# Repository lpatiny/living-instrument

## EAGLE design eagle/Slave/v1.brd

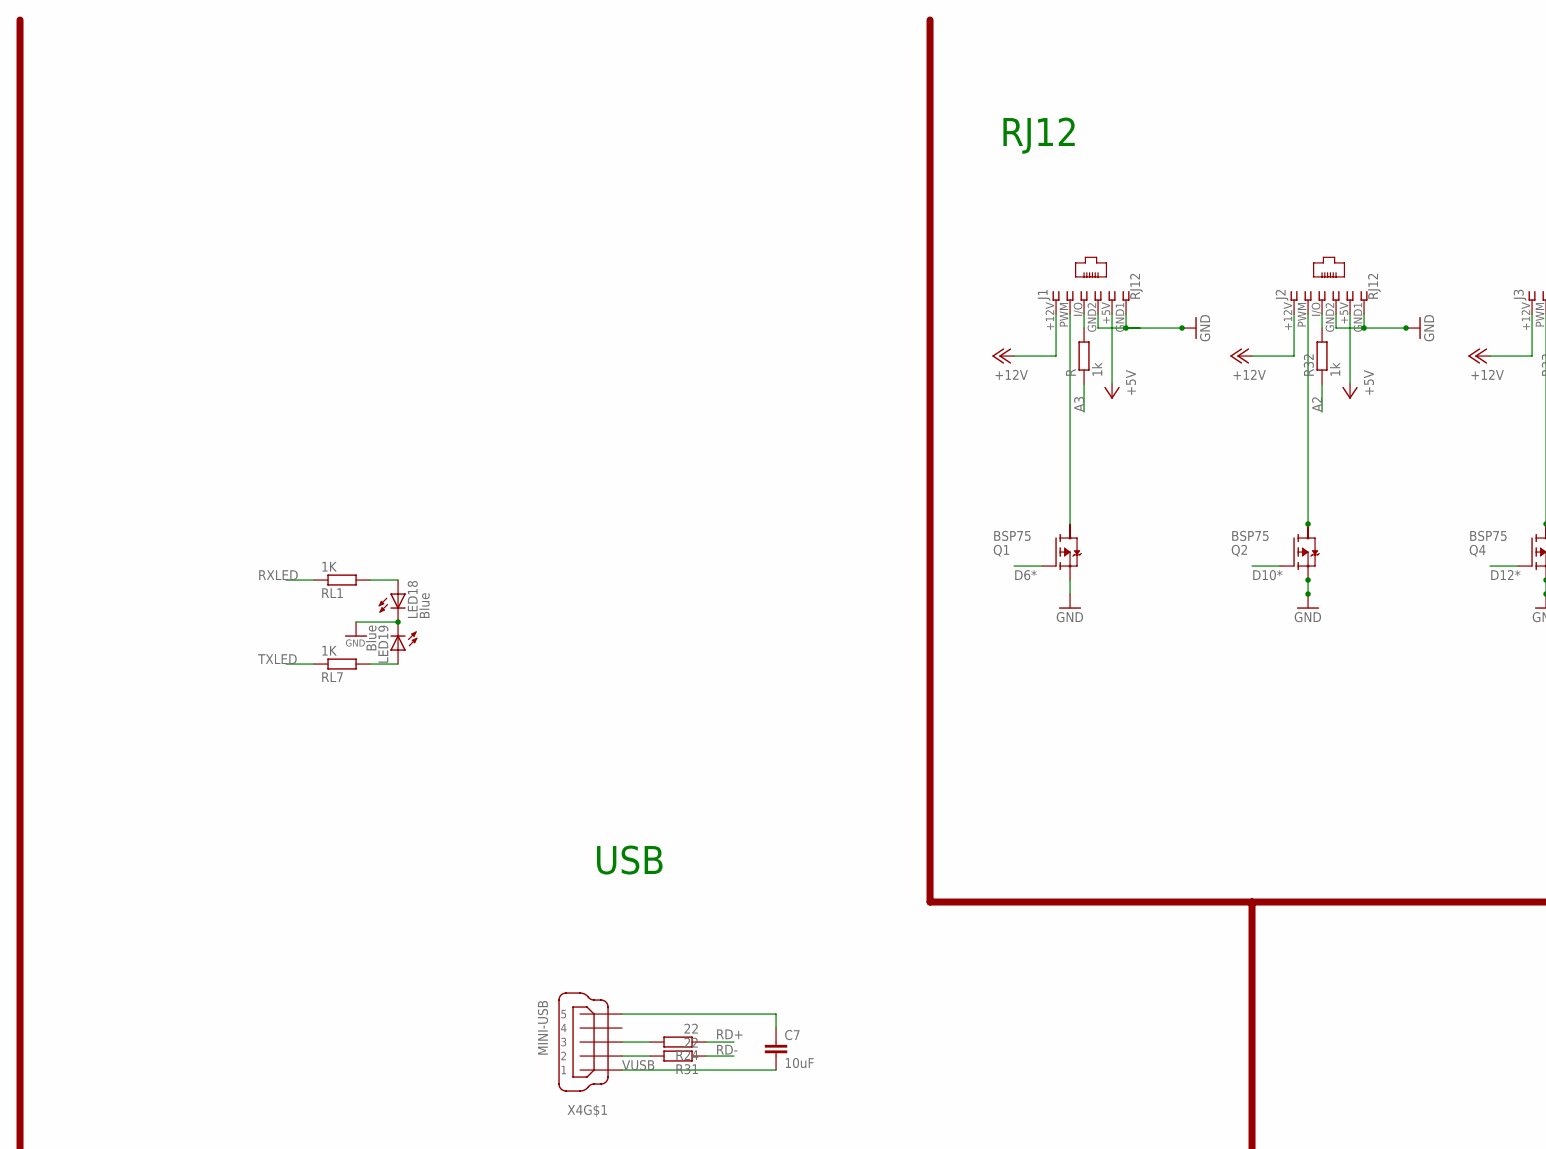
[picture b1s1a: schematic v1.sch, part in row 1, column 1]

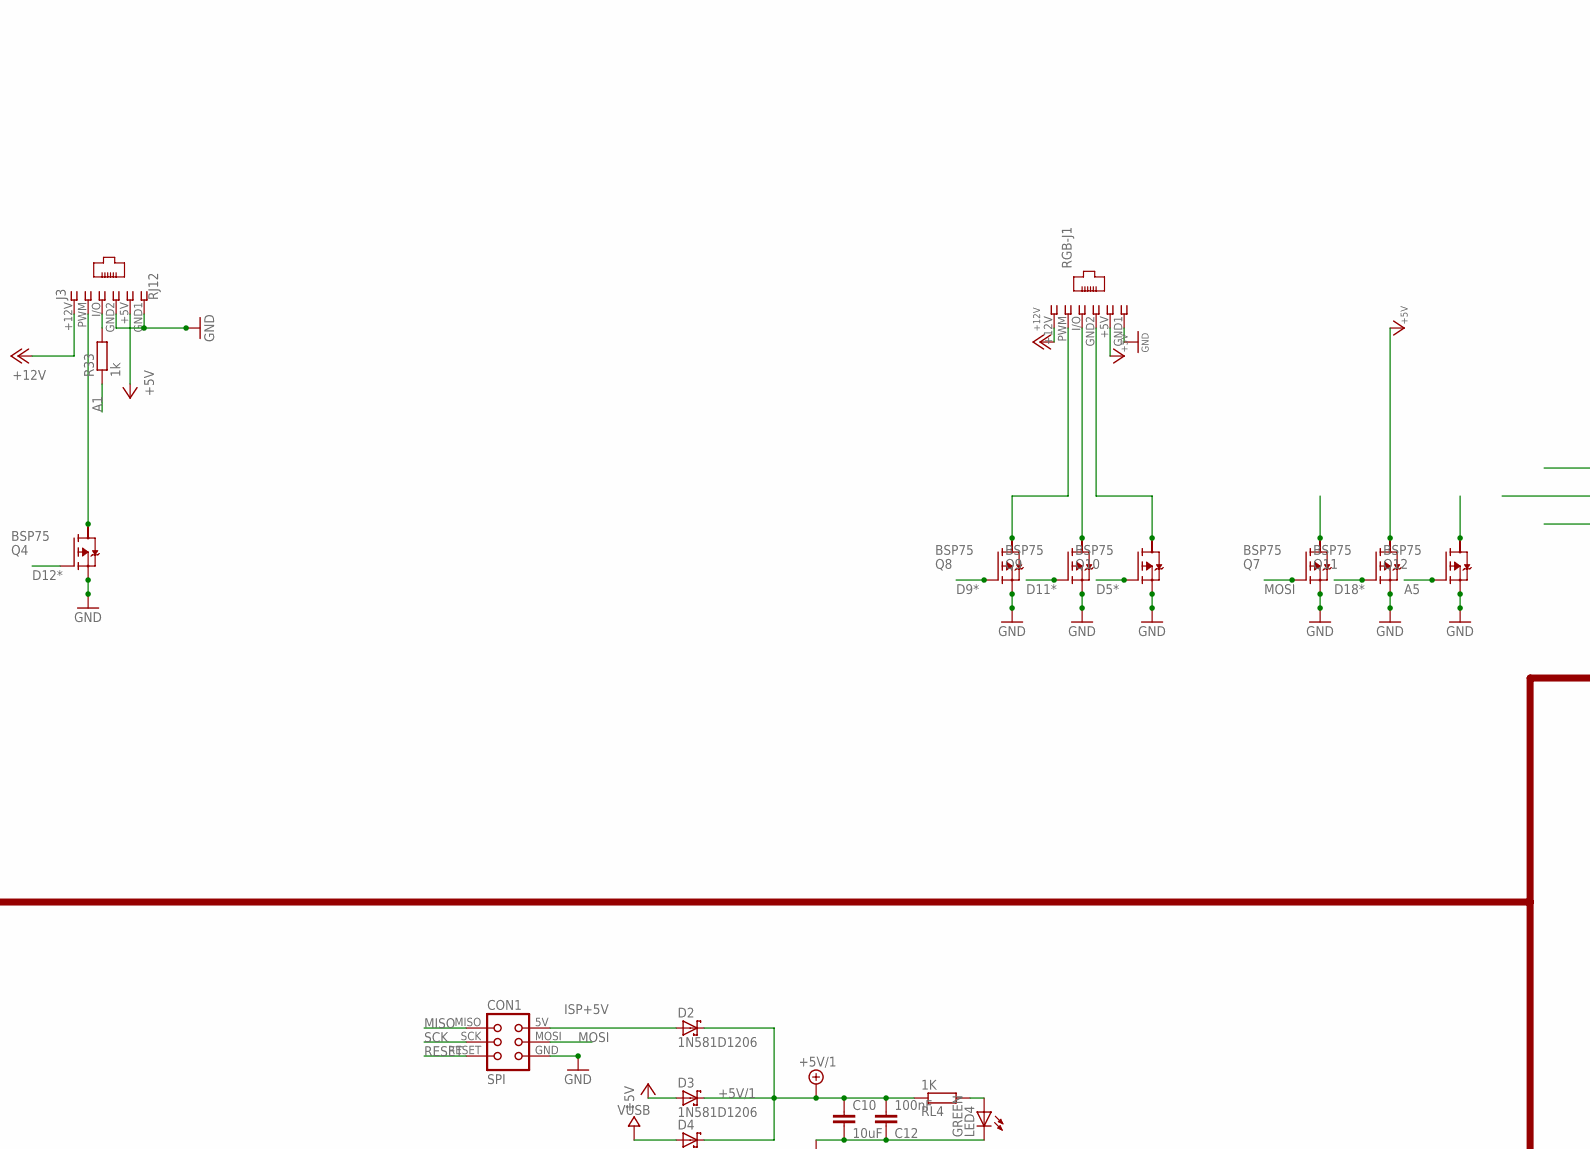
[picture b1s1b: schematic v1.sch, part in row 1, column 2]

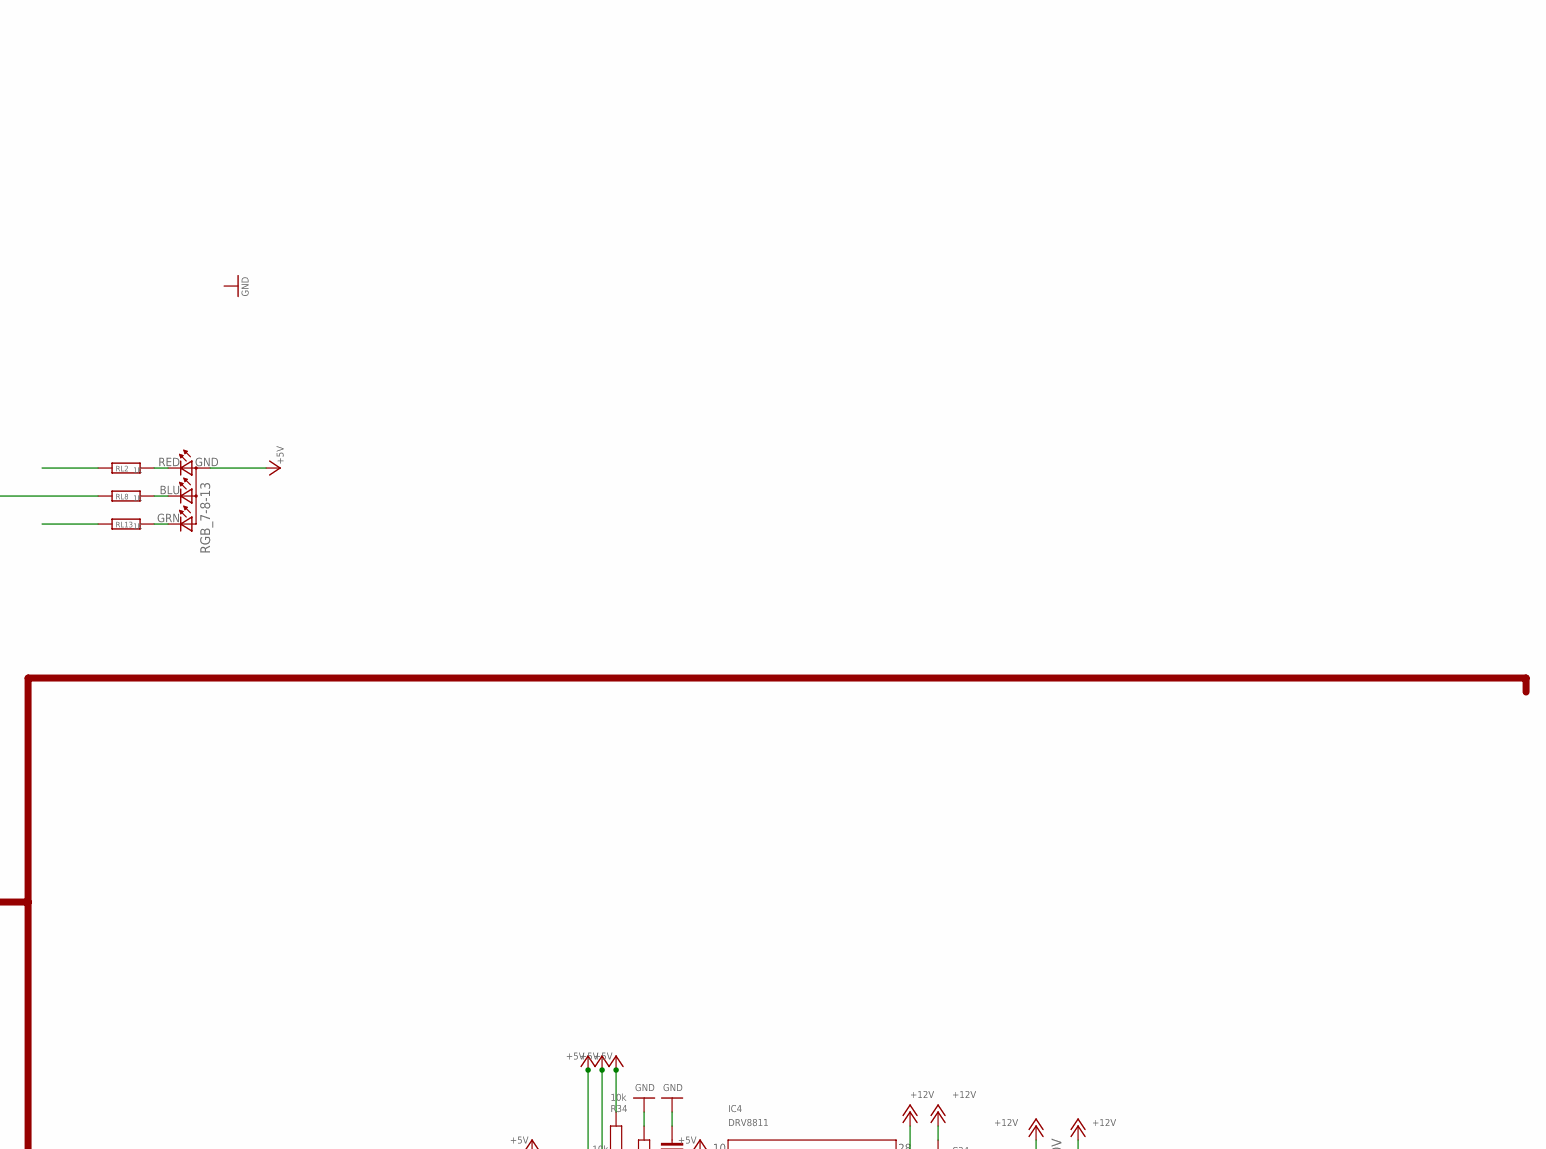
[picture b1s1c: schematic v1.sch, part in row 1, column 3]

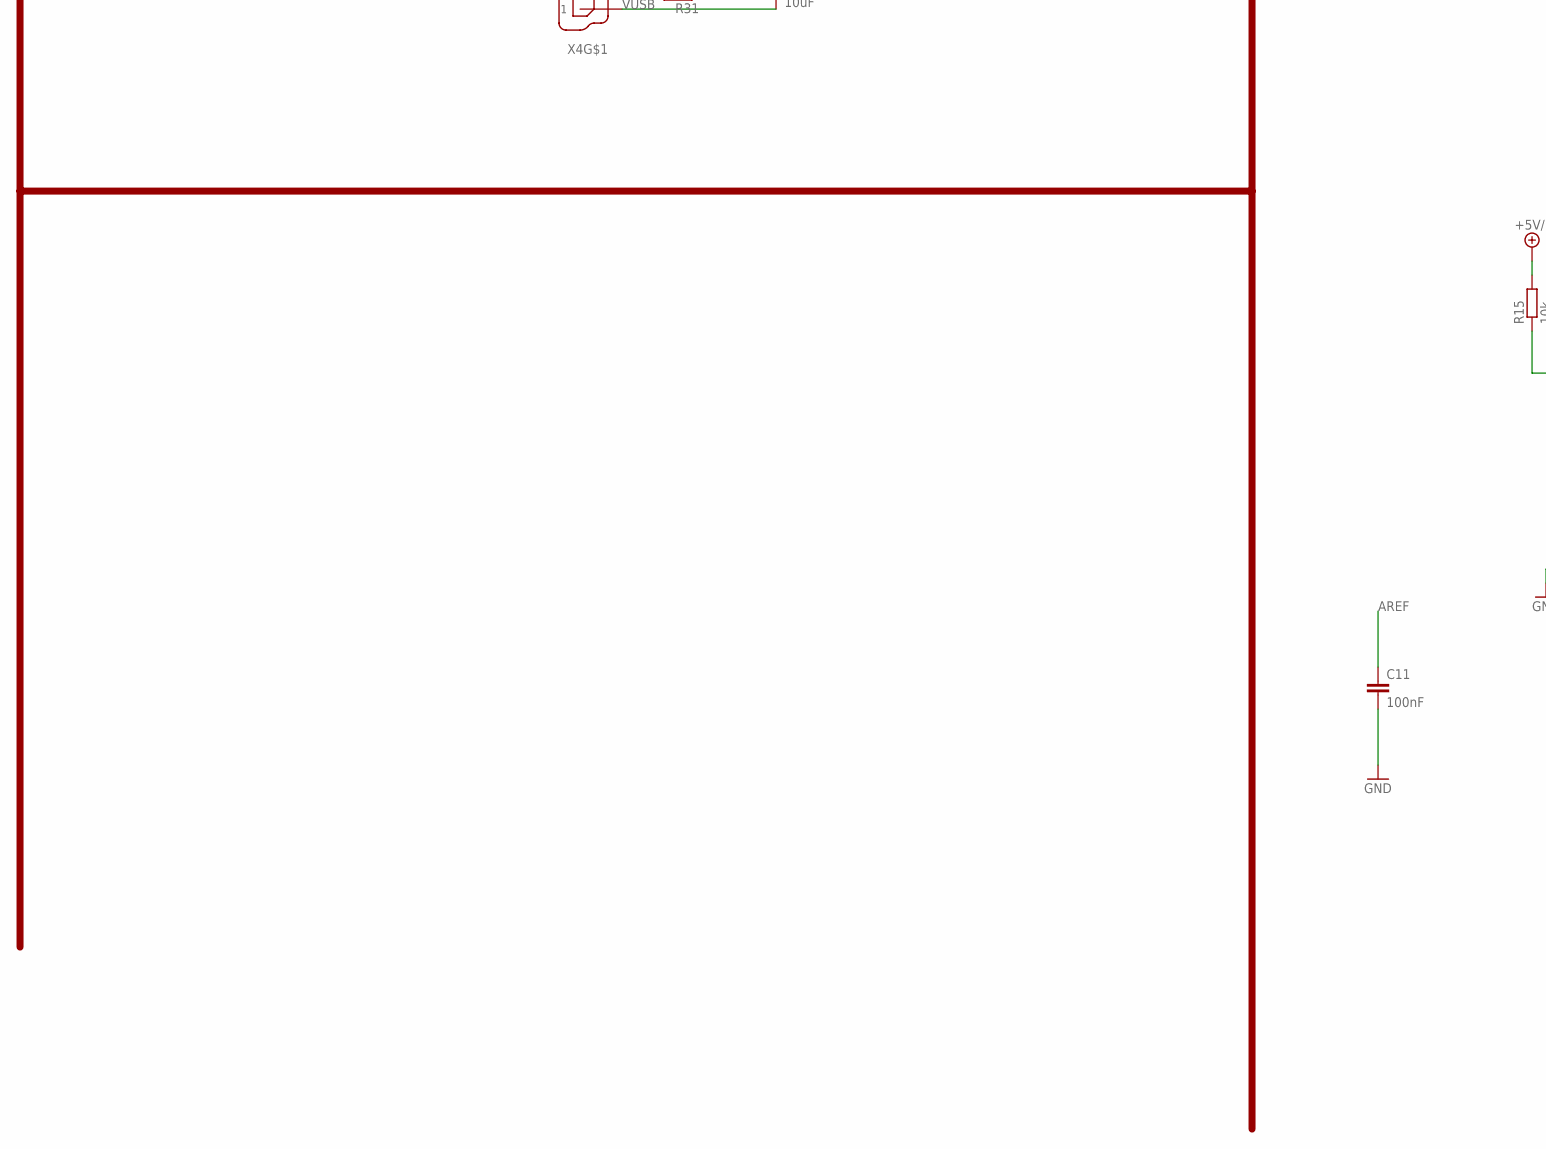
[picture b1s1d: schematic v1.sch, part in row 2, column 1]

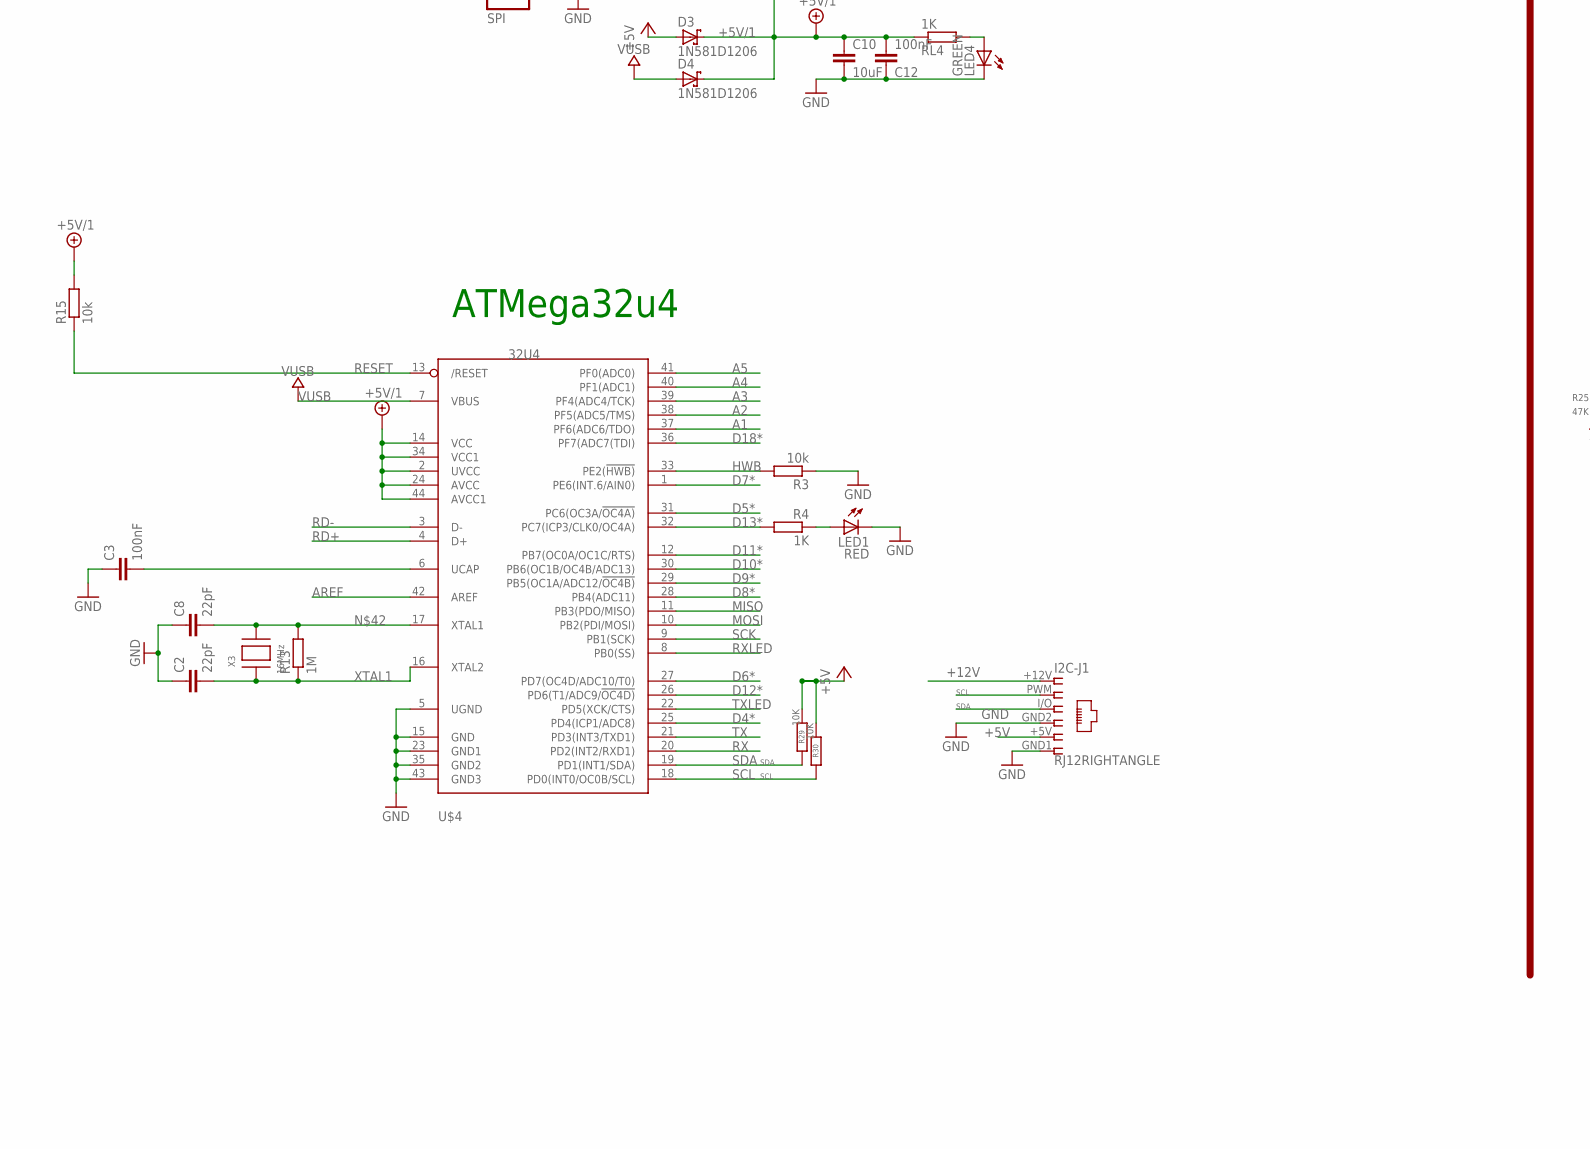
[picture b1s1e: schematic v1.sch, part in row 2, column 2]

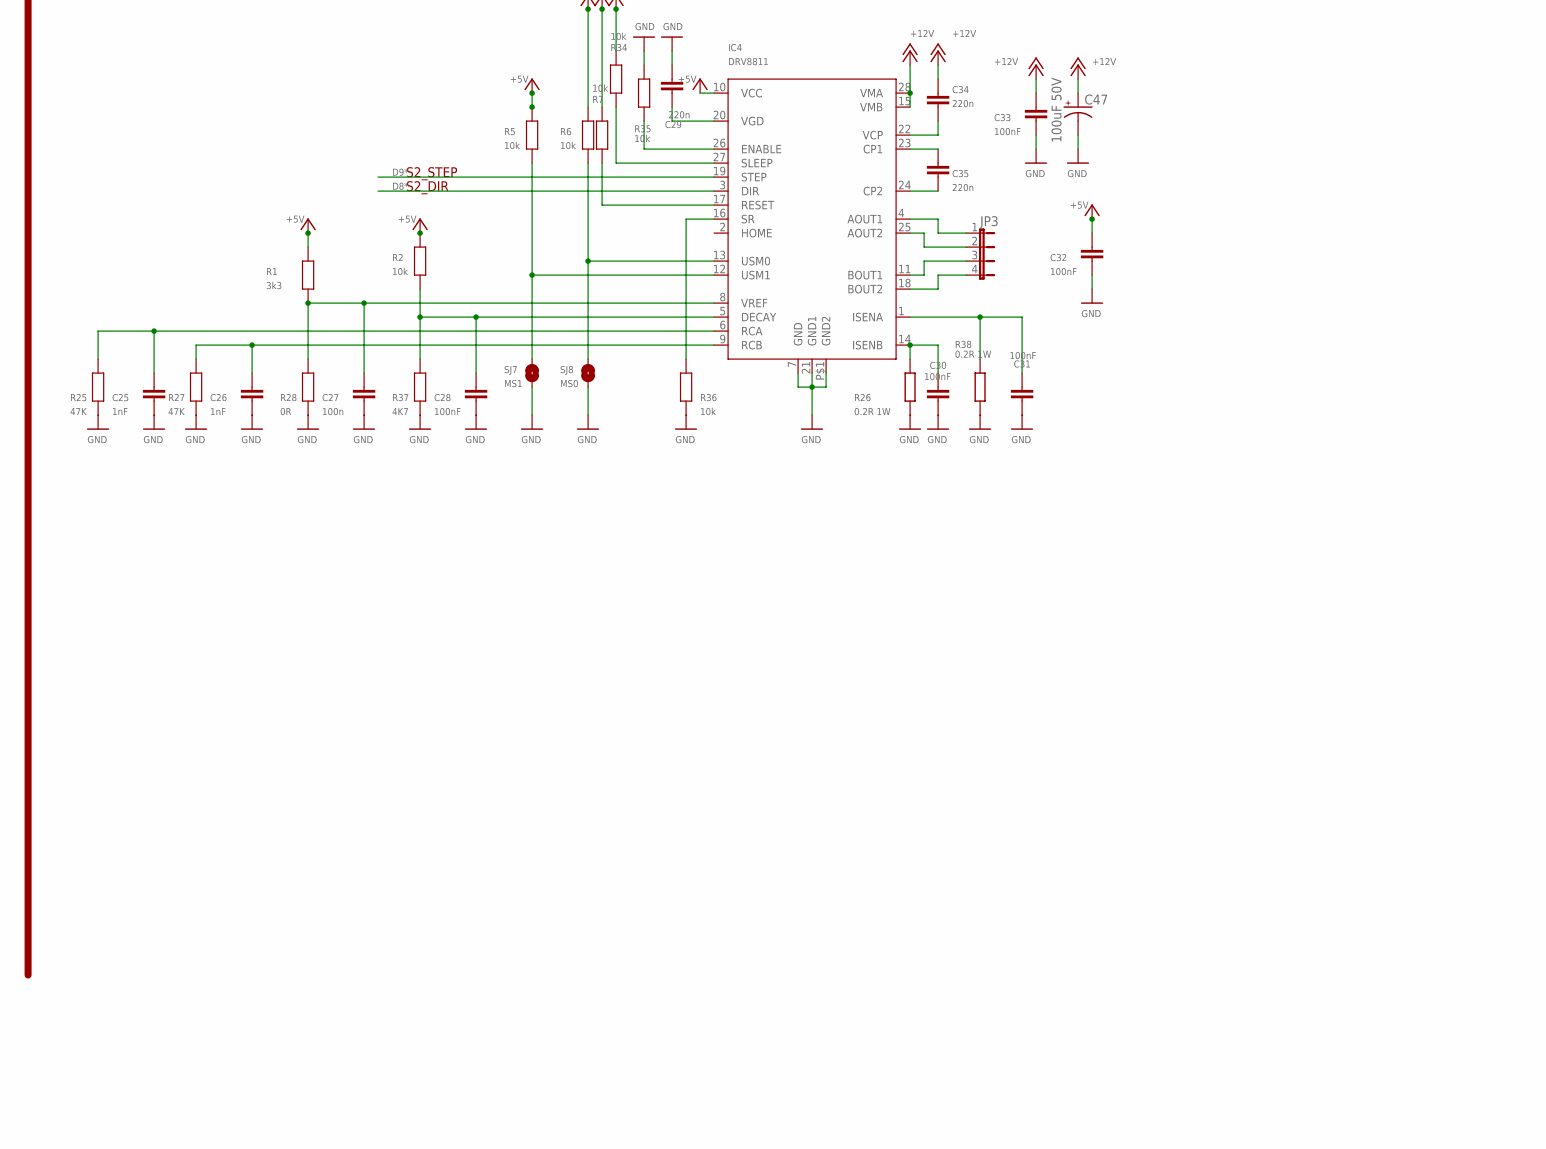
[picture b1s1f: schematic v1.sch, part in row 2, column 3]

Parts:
C2, C8: 22pF; C1206
C3, C11, C12: 100nF; C1206
C7, C10: 10uF; C1206
C25, C26: 1nF; 0805
C27: 100n; 0805
C28, C31, C32, C33: 100nF; 0805
C29, C34, C35: 220n; 0805
C30: 100nF; 0603
C47: 100uF 50V; PANASONIC_E
CON1: SPI; TC2030-MCP-NL
D2, D3, D4: 1N581D1206; LED-1206
I2C-J1: RJ12RIGHTANGLE; RJ12-RIGHTANGLE
IC4: DRV8811; HTSSOP28
J1, J2, J3: RJ12; RJ12-RIGHTANGLE
JP3: JP4E; JP4
LED1: RED; CHIP-LED0805
LED4: GREEN; CHIP-LED0805
LED18, LED19: Blue; CHIP-LED0805
Q1, Q2, Q4, Q7, Q8, Q9, Q10, Q11, Q12: BSP75; PG-SOT-223
R, R32, R33: 1k; R0805
R1: 3k3; 0805
R2, R5, R6, R7, R34, R35, R36: 10k; 0805
R3, R15: 10k; M0805
R4: 1K; R0805
R13: 1M; R1206
R24, R31: 22; M1206
R25, R27: 47K; 0805
R26, R38: 0.2R 1W; R2010
R28: 0R; 0805
R29, R30: 10K; M0805
R37: 4K7; 0805
RGB-J1: RJ12; RJ12-RIGHTANGLE
RGB_7-8-13: TOPLED-3; LED-TRICOLOR-THROUGHHOLE
RL1, RL4, RL7: 1K; R0805
RL2, RL8, RL13: 1K; M1206
SJ7: MS1; SJ
SJ8: MS0; SJ
U$4: 32U4; TQFP44
X3: 16MHz; NX6035
X4: MINI-USB; 32005-201

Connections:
+5V: C32.1, D3.A, I2C-J1.+5V (5), IC4.10 (VCC), J1.+5V (5), J2.+5V (5), J3.+5V (5), Q11.2 (D), R1.2, R2.2, R5.2, R6.2, R7.2, R29.1, R30.1, R34.2, RGB-J1.+5V (5)
+5V1: RGB_7-8-13.GND (A2)
+5V/1: C10.1, C12.2, D2.C, D3.C, D4.C, R15.2, RL4.1, U$4.2 (UVCC), U$4.14 (VCC), U$4.24 (AVCC), U$4.34 (VCC1), U$4.44 (AVCC1)
+12V: C33.1, C34.1, C47.+, I2C-J1.+12V (1), IC4.15 (VMB), IC4.28 (VMA), J1.+12V (1), J2.+12V (1), J3.+12V (1), RGB-J1.+12V (1)
A1: R33.1, U$4.37 (PF6(ADC6/TDO))
A2: R32.1, U$4.38 (PF5(ADC5/TMS))
A3: R.1, U$4.39 (PF4(ADC4/TCK))
A4: U$4.40 (PF1(ADC1))
A5: Q12.1 (G), U$4.41 (PF0(ADC0))
AREF: C11.1, U$4.42 (AREF)
D4*: U$4.25 (PD4(ICP1/ADC8))
D5*: Q10.1 (G), U$4.31 (PC6(OC3A/!OC4A))
D6*: Q1.1 (G), U$4.27 (PD7(OC4D/ADC10/T0))
D7*: U$4.1 (PE6(INT.6/AIN0))
D8*: IC4.3 (DIR), U$4.28 (PB4(ADC11))
D9*: IC4.19 (STEP), Q8.1 (G), U$4.29 (PB5(OC1A/ADC12/!OC4B))
D10*: Q2.1 (G), U$4.30 (PB6(OC1B/OC4B/ADC13))
D11*: Q9.1 (G), U$4.12 (PB7(OC0A/OC1C/RTS))
D12*: Q4.1 (G), U$4.26 (PD6(T1/ADC9/!OC4D))
D13*: R4.2, U$4.32 (PC7(ICP3/CLK0/OC4A))
D18*: Q11.1 (G), U$4.36 (PF7(ADC7(TDI))
D+USB: R24.2, X4.3
D-USB: R31.2, X4.2
GND: C2.1, C3.1, C7.1, C8.1, C10.2, C11.2, C12.1, C25.2, C26.2, C27.2, C28.2, C29.2, C30.2, C31.2, C32.2, C33.2, C47.-, CON1.GND, I2C-J1.GND1 (6), I2C-J1.GND2 (4), IC4.7 (GND), IC4.21 (GND1), IC4.P$1 (GND2), J1.GND1 (6), J1.GND2 (4), J2.GND1 (6), J2.GND2 (4), J3.GND1 (6), J3.GND2 (4), LED1.C, LED4.C, LED18.C, LED19.C, Q1.3 (S), Q2.3 (S), Q4.3 (S), Q7.3 (S), Q8.3 (S), Q9.3 (S), Q10.3 (S), Q11.3 (S), Q12.3 (S), R3.1, R25.1, R26.1, R27.1, R28.1, R35.1, R36.1, R37.1, R38.1, RGB-J1.GND1 (6), SJ7.1, SJ8.1, U$4.5 (UGND), U$4.15 (GND), U$4.23 (GND1), U$4.35 (GND2), U$4.43 (GND3), X4.5
HWB: R3.2, U$4.33 (PE2(!HWB))
ISP+5V: CON1.5V (VCC), D2.A
MISO: CON1.MISO, U$4.11 (PB3(PDO/MISO))
MOSI: CON1.MOSI, Q7.1 (G), U$4.10 (PB2(PDI/MOSI))
unnamed: J3.PWM (2), Q4.2 (D)
unnamed: J2.I/O (3), R32.2
unnamed: IC4.18 (BOUT2), JP3.4
unnamed: LED1.A, R4.1
unnamed: IC4.25 (AOUT2), JP3.2
unnamed: Q10.2 (D), RGB-J1.GND2 (4)
unnamed: J3.I/O (3), R33.2
unnamed: LED18.A, RL1.2
unnamed: C35.2, IC4.24 (CP2)
unnamed: IC4.26 (ENABLE), R35.2
unnamed: LED4.A, RL4.2
unnamed: LED19.A, RL7.2
unnamed: C3.2, U$4.6 (UCAP)
unnamed: J1.I/O (3), R.2
unnamed: RGB_7-8-13.RED (CRED), RL2.2
unnamed: RGB_7-8-13.BLU (CBLUE), RL8.2
unnamed: RGB_7-8-13.GRN (CGREEN), RL13.2
unnamed: J2.PWM (2), Q2.2 (D)
unnamed: C35.1, IC4.23 (CP1)
unnamed: C34.2, IC4.22 (VCP)
unnamed: J1.PWM (2), Q1.2 (D)
unnamed: C29.1, IC4.20 (VGD)
unnamed: C31.1, IC4.1 (ISENA), R38.2
unnamed: C30.1, IC4.14 (ISENB), R26.2
unnamed: C8.2, R13.2, U$4.17 (XTAL1), X3.P$2
unnamed: C28.1, IC4.5 (DECAY), R2.1, R37.2
unnamed: C25.1, IC4.6 (RCA), R25.2
unnamed: C26.1, IC4.9 (RCB), R27.2
unnamed: IC4.27 (SLEEP), R34.1
unnamed: IC4.17 (RESET), R7.1
unnamed: C27.1, IC4.8 (VREF), R1.1, R28.2
unnamed: Q9.2 (D), RGB-J1.I/O (3)
unnamed: IC4.12 (USM1), R5.1, SJ7.2
unnamed: IC4.13 (USM0), R6.1, SJ8.2
unnamed: IC4.16 (SR), R36.2
unnamed: IC4.4 (AOUT1), JP3.1
unnamed: IC4.11 (BOUT1), JP3.3
unnamed: Q8.2 (D), RGB-J1.PWM (2)
RD+: R24.1, U$4.4 (D+)
RD-: R31.1, U$4.3 (D-)
RESET: CON1.RESET, R15.1, U$4.13 (/RESET)
RX: U$4.20 (PD2(INT2/RXD1))
RXLED: RL1.1, U$4.8 (PB0(SS))
SCK: CON1.SCK, U$4.9 (PB1(SCK))
SCL: I2C-J1.PWM (2), R30.2, U$4.18 (PD0(INT0/OC0B/SCL))
SDA: I2C-J1.I/O (3), R29.2, U$4.19 (PD1(INT1/SDA))
TX: U$4.21 (PD3(INT3/TXD1))
TXLED: RL7.1, U$4.22 (PD5(XCK/CTS))
VUSB: C7.2, D4.A, U$4.7 (VBUS), X4.1
XTAL1: C2.2, R13.1, U$4.16 (XTAL2), X3.P$1

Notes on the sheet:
RJ12
ATMega32u4
USB
S2_DIR
S2_STEP

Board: 2 copper layers, 80 parts (24 on the bottom side), 72 nets, no tracks yet.

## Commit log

2017-02-01 Starting of eagle scheme
2017-02-01 add cad
2017-02-01 rename to Slave
2017-02-01 Rename
2017-02-02 Update eagle
2017-02-03 first try with FreeCAD. Added an interéediary plate

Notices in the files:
parts and their libraries:
lpatiny: ©2009 ROFA.cz - modified and updated by Robert Darlington ‹rdarlington@gmail.com›
freetronics-original: Licensing: CC v3.0 Share-Alike You are welcome to use this library for commercial purposes.
